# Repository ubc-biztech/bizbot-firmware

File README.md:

# bizbot-firmware
This firmware controls the low-level robot layer for BizBot.

# BizBot ESP32 Firmware

This firmware controls the low-level robot layer for BizBot.

## Responsibilities

- Read IMU
- Read encoders
- Control motors
- Run balance PID loop
- Receive high-level commands over USB serial or local Wi-Fi
- Send telemetry to host
- Enforce safety limits

## Current Prototype Architecture

Laptop -> USB Serial or Wi-Fi TCP -> ESP32 -> Motor Driver -> Motors

## Command Protocol

Send commands to the ESP32 over USB serial at 115200 baud or Wi-Fi TCP port
3333. Each command must end with a newline (`\n`).

```text
ENABLE
DISABLE
STOP
CMD_VEL <linear> <angular>
GET_STATE
```

`linear` and `angular` accept normalized values from `-1.0` to `1.0`.

```text
ENABLE
CMD_VEL 0.2 0.0
GET_STATE
STOP
DISABLE
```

## Local Wi-Fi control

The ESP32 creates its own 2.4 GHz access point; a router or internet connection
is not required.

```text
SSID: BizBot-Control
Password: bizbot-control
ESP32 address: 192.168.4.1
TCP control port: 3333
```

Change the prototype password in `src/config.h` before operating in public.
Only one TCP controller is accepted. While it is connected, Wi-Fi owns the
command input and USB remains a debug console. A Wi-Fi disconnect immediately
disables the robot and restores USB command input.

### Connect and test

1. Keep the wheels off the ground and leave the motor power disconnected for
   the initial communications test.
2. Install the host dependencies:

   ```bash
   python3 -m pip install -r requirements.txt
   ```

3. Build and upload using the PlatformIO IDE, or its CLI:

   ```bash
   pio run -d firmware --target upload
   ```

4. Open the USB serial monitor at 115200 baud. On a successful boot it prints:

   ```text
   WiFi AP: BizBot-Control
   WiFi control: 192.168.4.1:3333
   ```

5. On the laptop, join the `BizBot-Control` Wi-Fi network using the password
   above. The laptop may report that this network has no internet; that is
   expected.
6. Start Wi-Fi keyboard control:

   ```bash
   python3 tools/keyboard_controls.py --transport wifi
   ```

   Use `W/A/S/D`, release the keys to stop, press `I` for state, and `Q` to
   stop, disable, and disconnect.

USB control remains available when no Wi-Fi TCP client is connected:

```bash
python3 tools/keyboard_controls.py --transport serial
```

The current PlatformIO configuration builds with `IMU_USE_STUB=1`. Stub builds
accept commands for communications testing but always force the hoverboard
output to zero. Do not set `IMU_USE_STUB=0` until the real IMU implementation
returns correctly oriented pitch and pitch-rate measurements. After installing
the real IMU, perform the first motor test with the chassis restrained and tune
the placeholder controller values before putting the wheels on the ground.

## Repo structure

```
bizbot-firmware/
├── firmware/
│   ├── platformio.ini
│   └── src/
│       ├── main.cpp
│       ├── config.h
│       │
│       ├── hal/
│       │   ├── Imu.h
│       │   ├── Imu.cpp
│       │   ├── MotorDriver.h
│       │   ├── MotorDriver.cpp
│       │   ├── Encoder.h
│       │   ├── Encoder.cpp
│       │   ├── Battery.h
│       │   └── Battery.cpp
│       │
│       ├── control/
│       │   ├── PID.h
│       │   ├── PID.cpp
│       │   ├── BalanceController.h
│       │   ├── BalanceController.cpp
│       │   ├── VelocityController.h
│       │   └── VelocityController.cpp
│       │
│       ├── comms/
│       │   ├── CommandParser.h
│       │   ├── CommandParser.cpp
│       │   ├── Telemetry.h
│       │   └── Telemetry.cpp
│       │
│       └── robot/
│           ├── RobotState.h
│           └── RobotState.cpp
│
├── sim/
│   ├── bizbot_mj/
│   └── bizbot_sim/
│
├── tools/
│   ├── keyboard_control.py
│   └── tuner/
│
└── README.md
```

```
main.cpp
  runs setup()
  runs loop()
  calls everything else

hal/
  talks directly to hardware

control/
  computes motor outputs

comms/
  parses laptop commands and sends telemetry

robot/
  shared state: enabled, target velocity, current angle, battery, etc.

tools/
  Python scripts that run on laptop for testing
```

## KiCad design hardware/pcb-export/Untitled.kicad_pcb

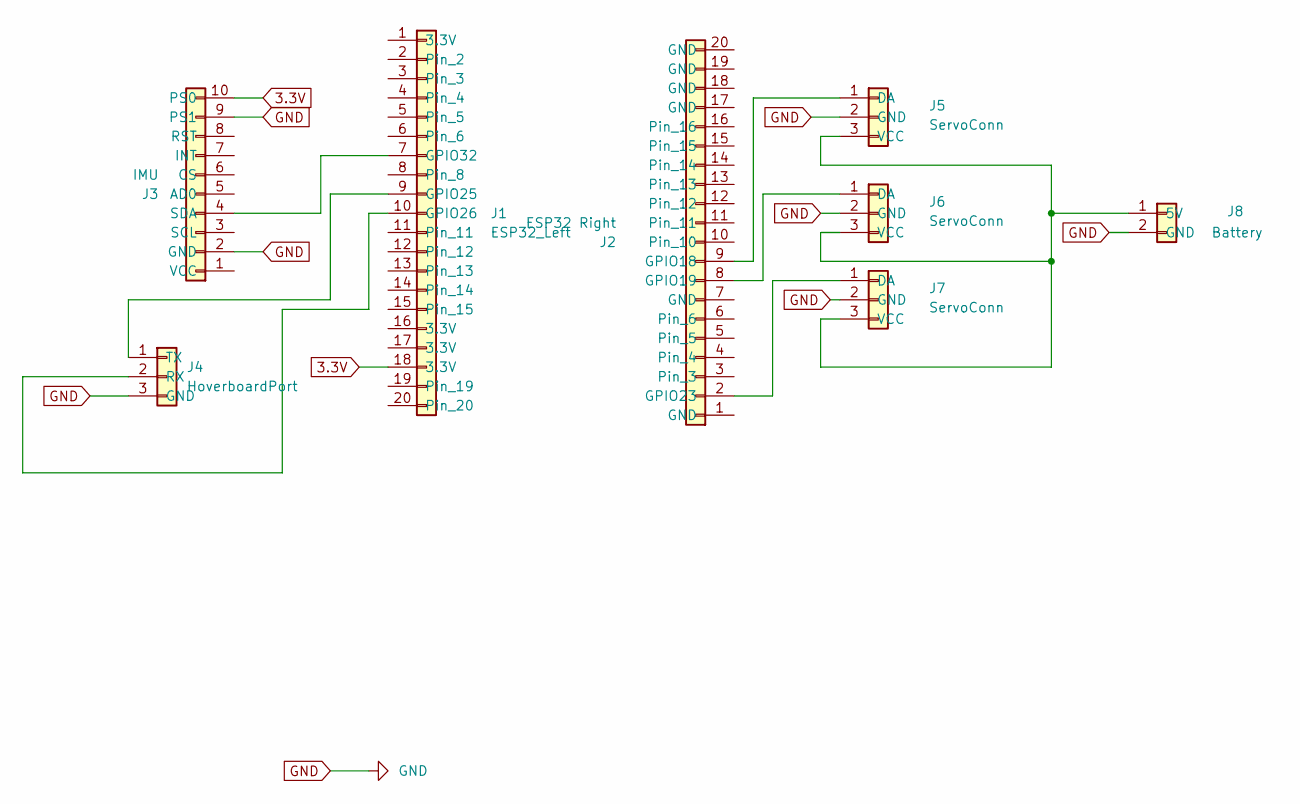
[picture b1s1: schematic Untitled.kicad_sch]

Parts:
J1: ESP32_Left; PinHeader_1x20_P2.54mm_Vertical
J2: ESP32 Right; PinHeader_1x20_P2.54mm_Vertical
J3: IMU; PinHeader_1x10_P2.54mm_Vertical
J4: HoverboardPort; PinHeader_1x03_P2.54mm_Vertical
J5, J6, J7: ServoConn; PinHeader_1x03_P2.54mm_Vertical
J8: Battery; PinHeader_1x02_P2.54mm_Vertical

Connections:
3.3V: J1.18 (3.3V), J3.10 (PS0)
GND: J3.2 (GND), J3.9 (PS1), J4.3 (GND), J5.2 (GND), J6.2 (GND), J7.2 (GND), J8.2 (GND)
unnamed: J1.9 (GPIO25), J4.1 (TX)
unnamed: J1.10 (GPIO26), J4.2 (RX)
unnamed: J1.7 (GPIO32), J3.4 (SDA)
unnamed: J2.9 (GPIO18), J5.1 (DA)
unnamed: J2.8 (GPIO19), J6.1 (DA)
unnamed: J2.2 (GPIO23), J7.1 (DA)
unnamed: J5.3 (VCC), J6.3 (VCC), J7.3 (VCC), J8.1 (5V)

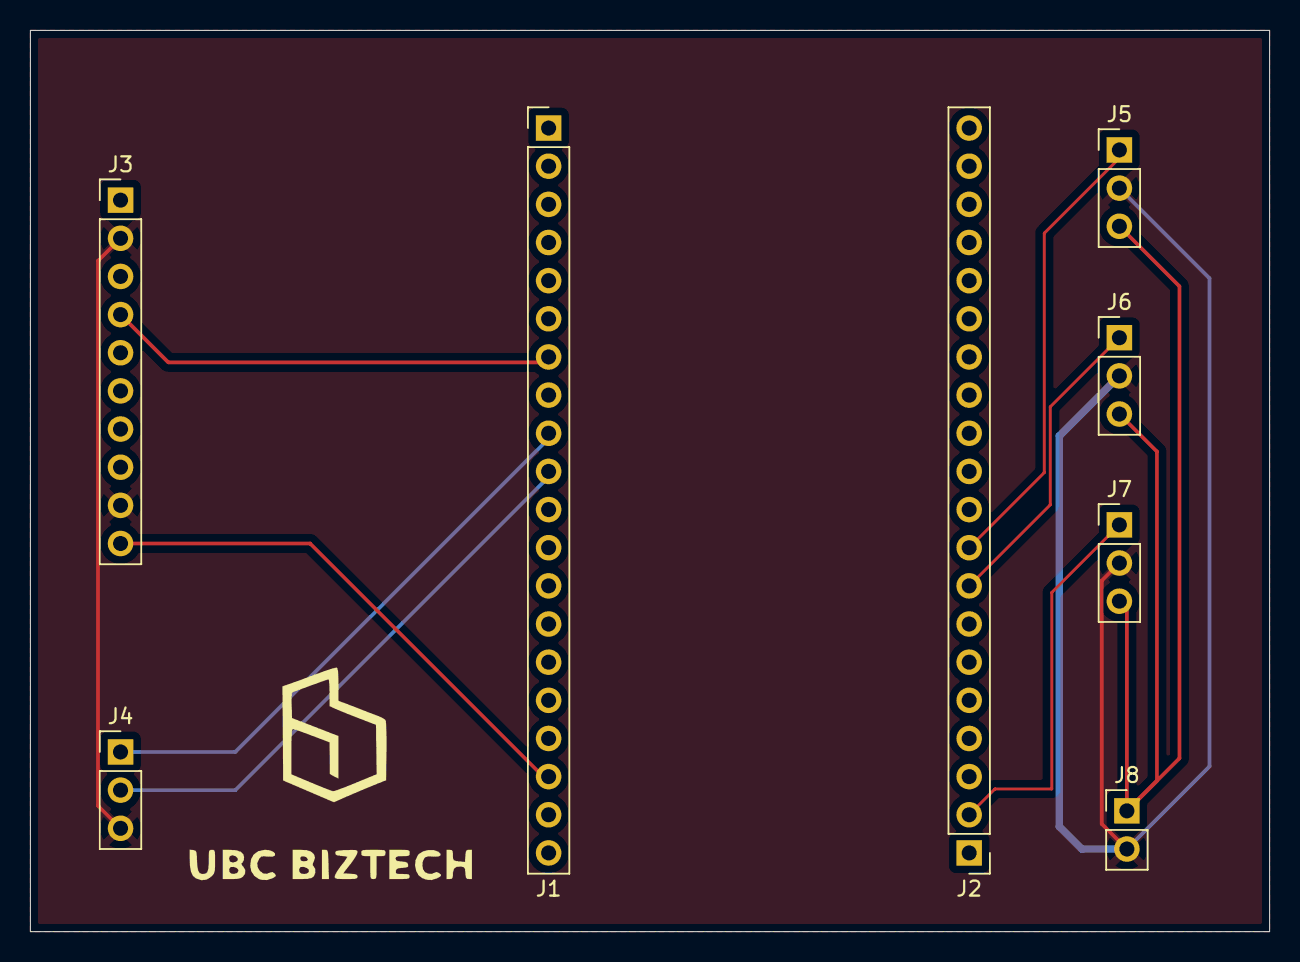
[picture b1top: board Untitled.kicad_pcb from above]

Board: 2 copper layers, 82.5 x 60.0 mm, 8 parts (0 on the bottom side), 9 nets.

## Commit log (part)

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2026-06-09 PlatformIO boiler plate
2026-06-09 Add smoke tests
2026-06-09 Provided template code
2026-06-09 define repo architecture
2026-06-09 Define global robot we will need for the PID loop. Also update readme info
2026-06-09 Add CommandParser Abstraction for firmware control
2026-06-09 ESP32 wiring
2026-06-09 Add Command Protocol doc in README
2026-06-11 Python script to command parser
2026-06-11 Add context and Handover for next steps
